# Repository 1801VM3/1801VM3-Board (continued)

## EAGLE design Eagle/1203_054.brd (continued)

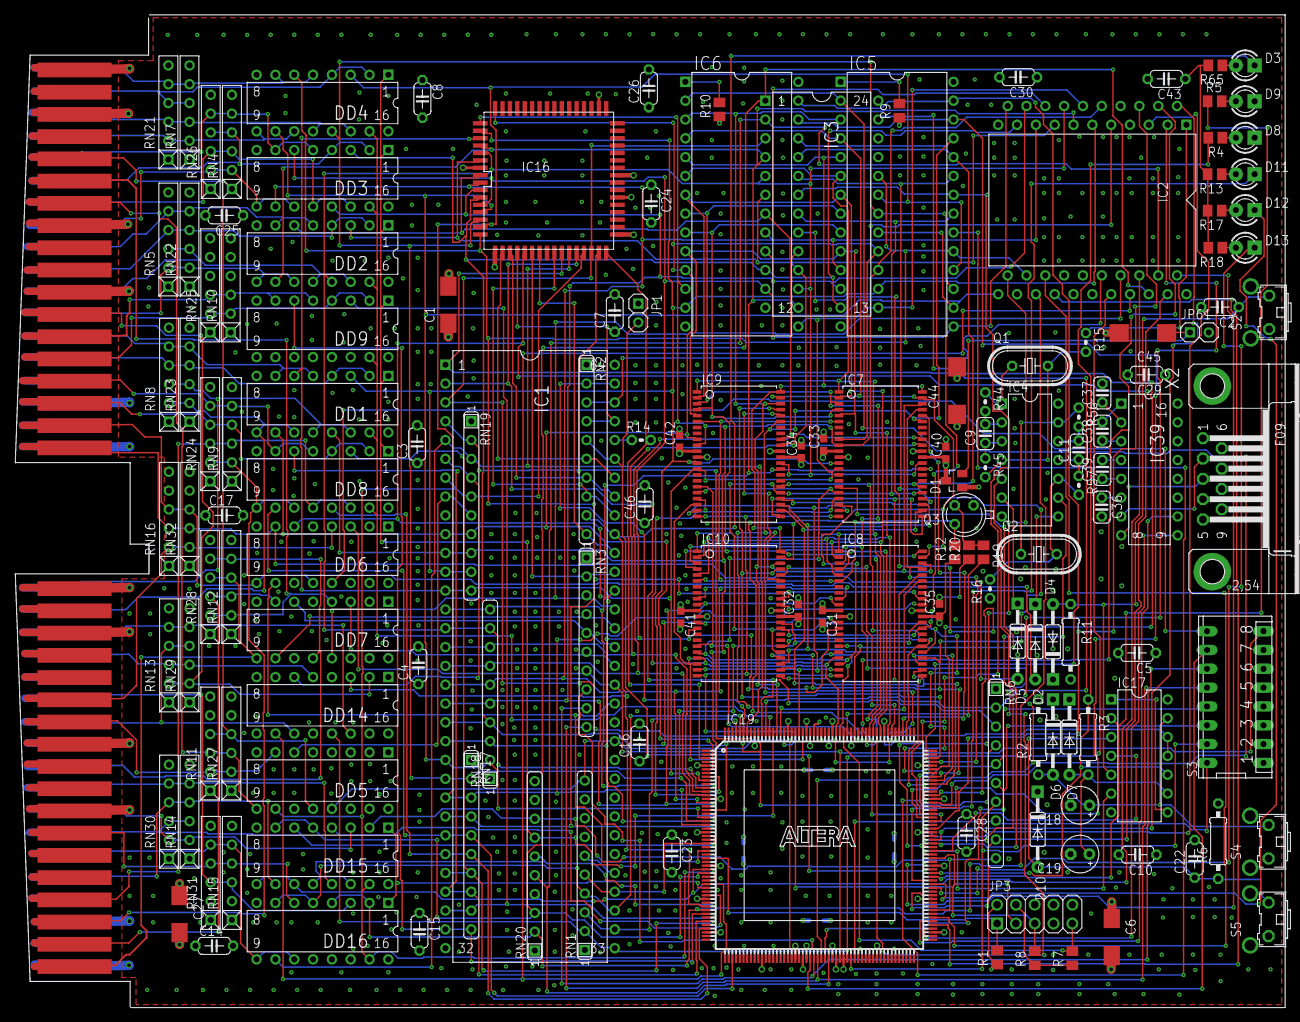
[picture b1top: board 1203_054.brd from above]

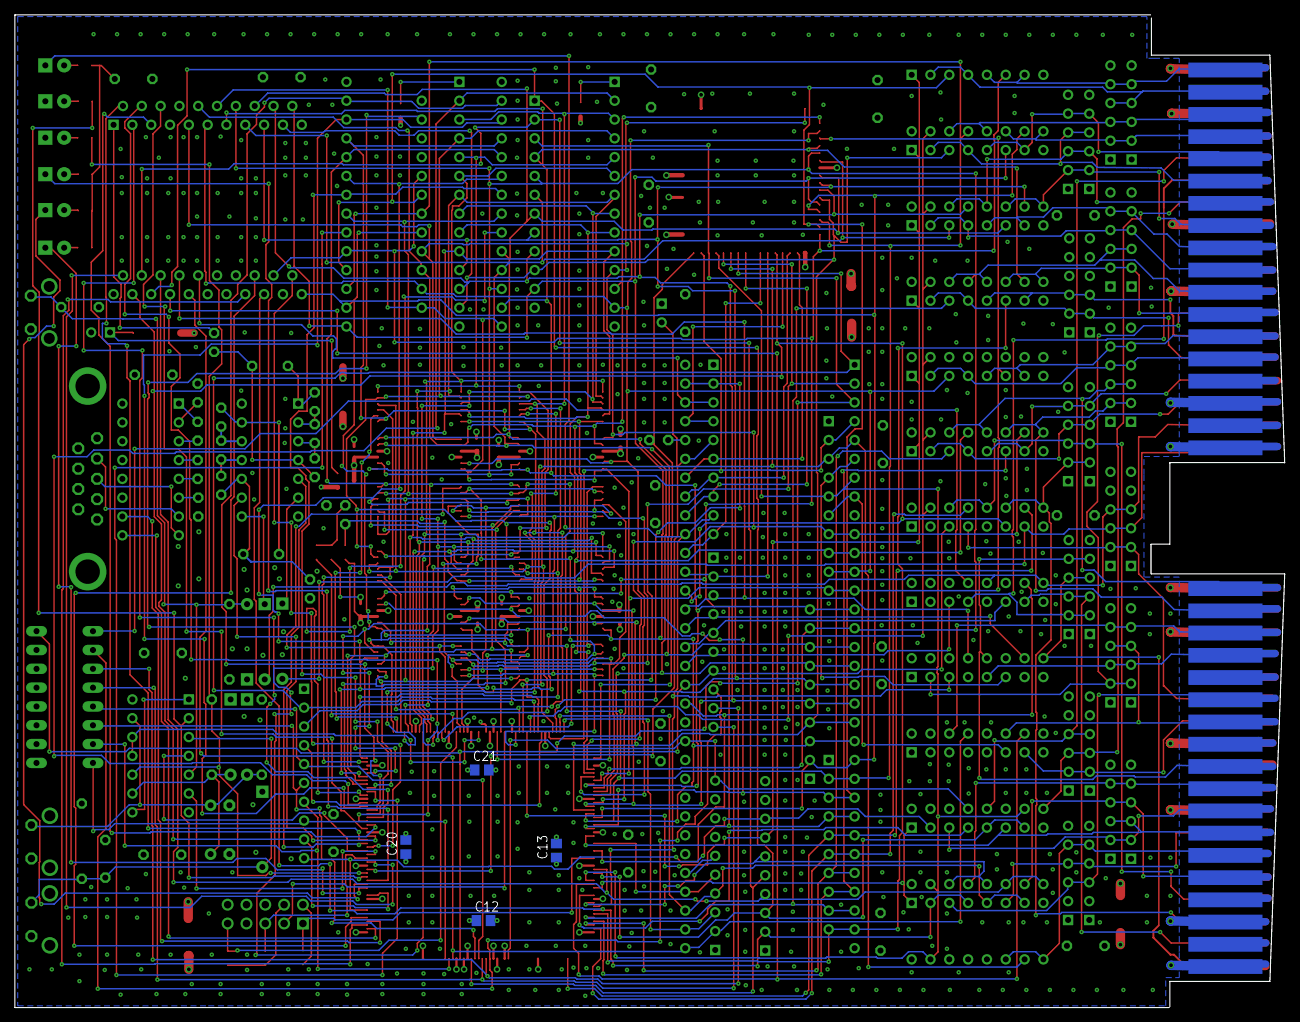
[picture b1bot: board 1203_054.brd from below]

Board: 3 copper layers, 171.4 x 134.0 mm, 154 parts (4 on the bottom side), 217 nets.

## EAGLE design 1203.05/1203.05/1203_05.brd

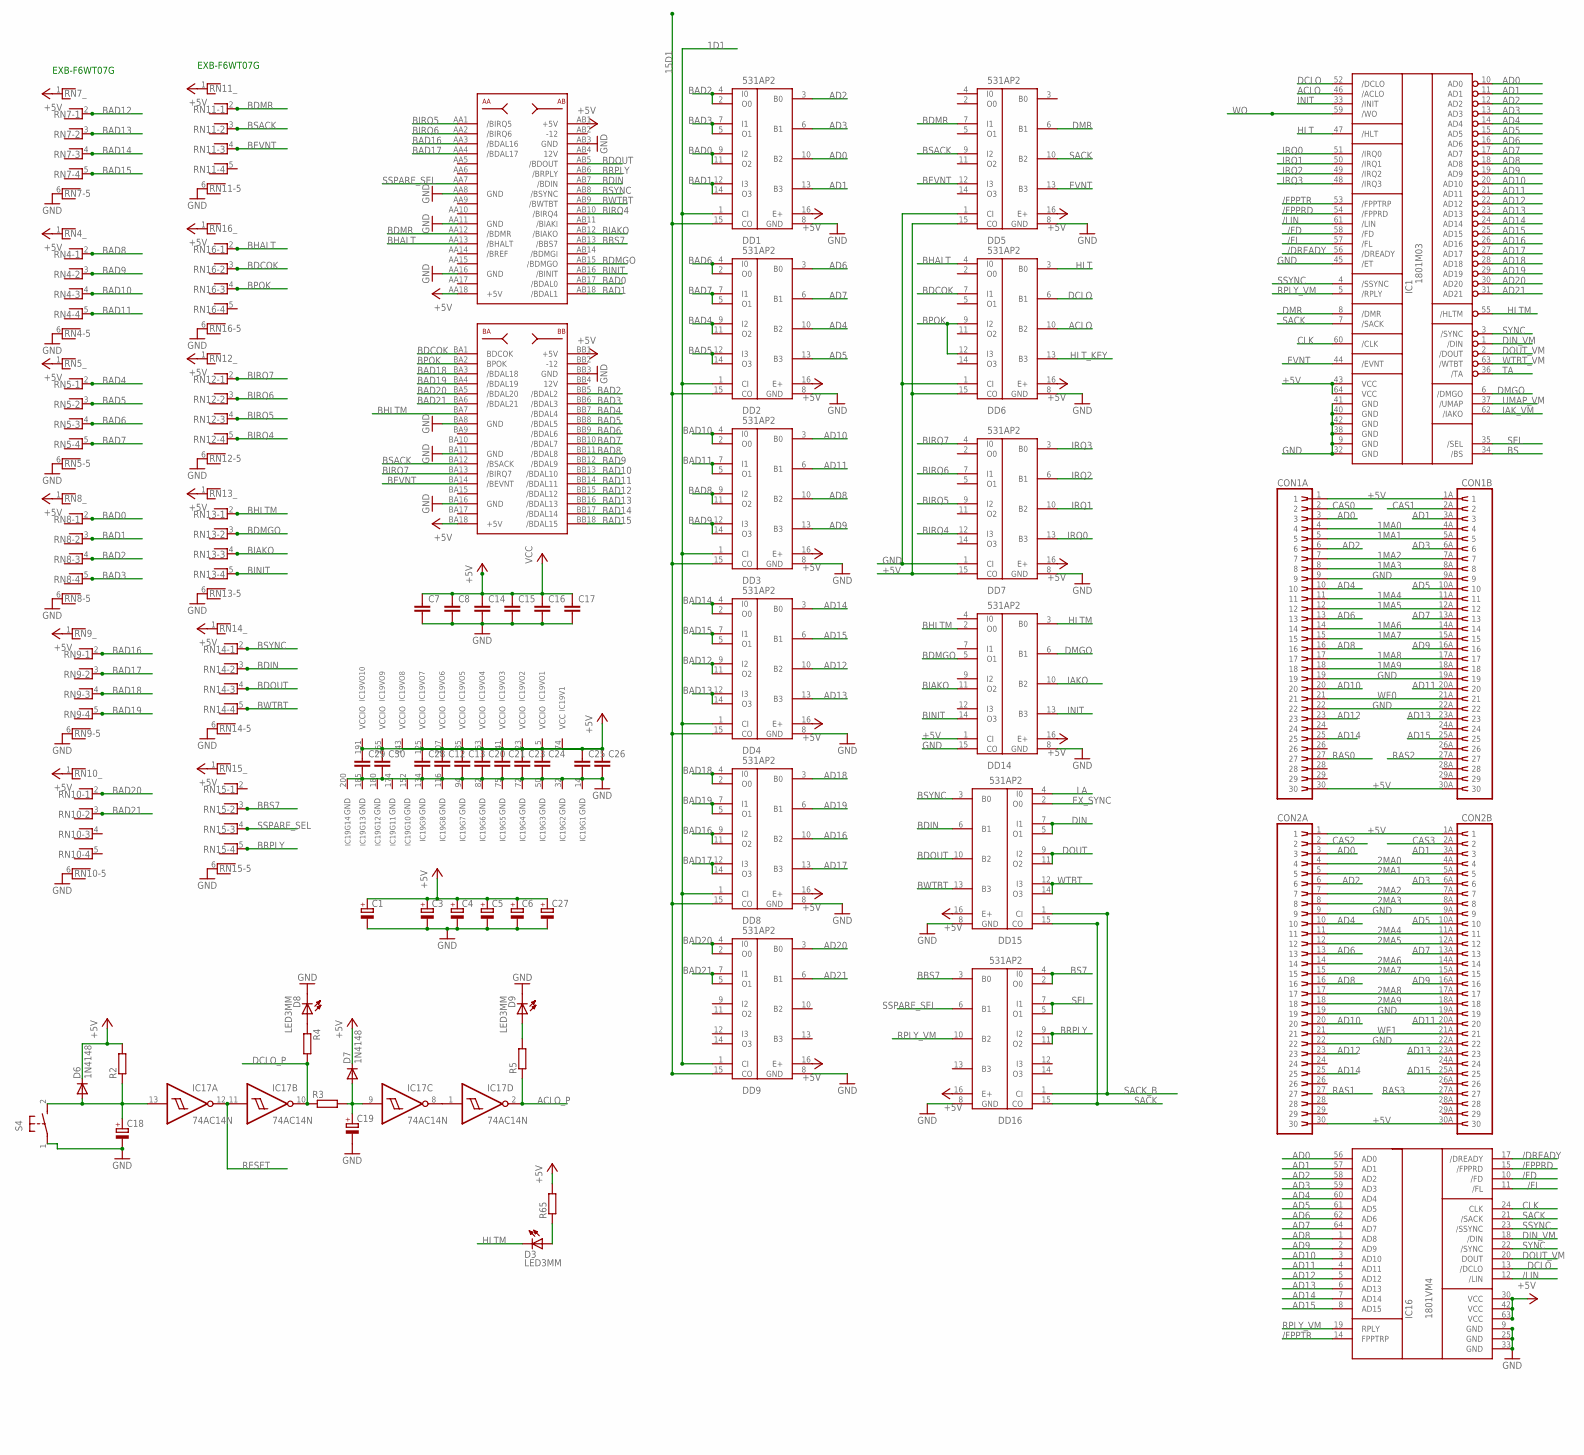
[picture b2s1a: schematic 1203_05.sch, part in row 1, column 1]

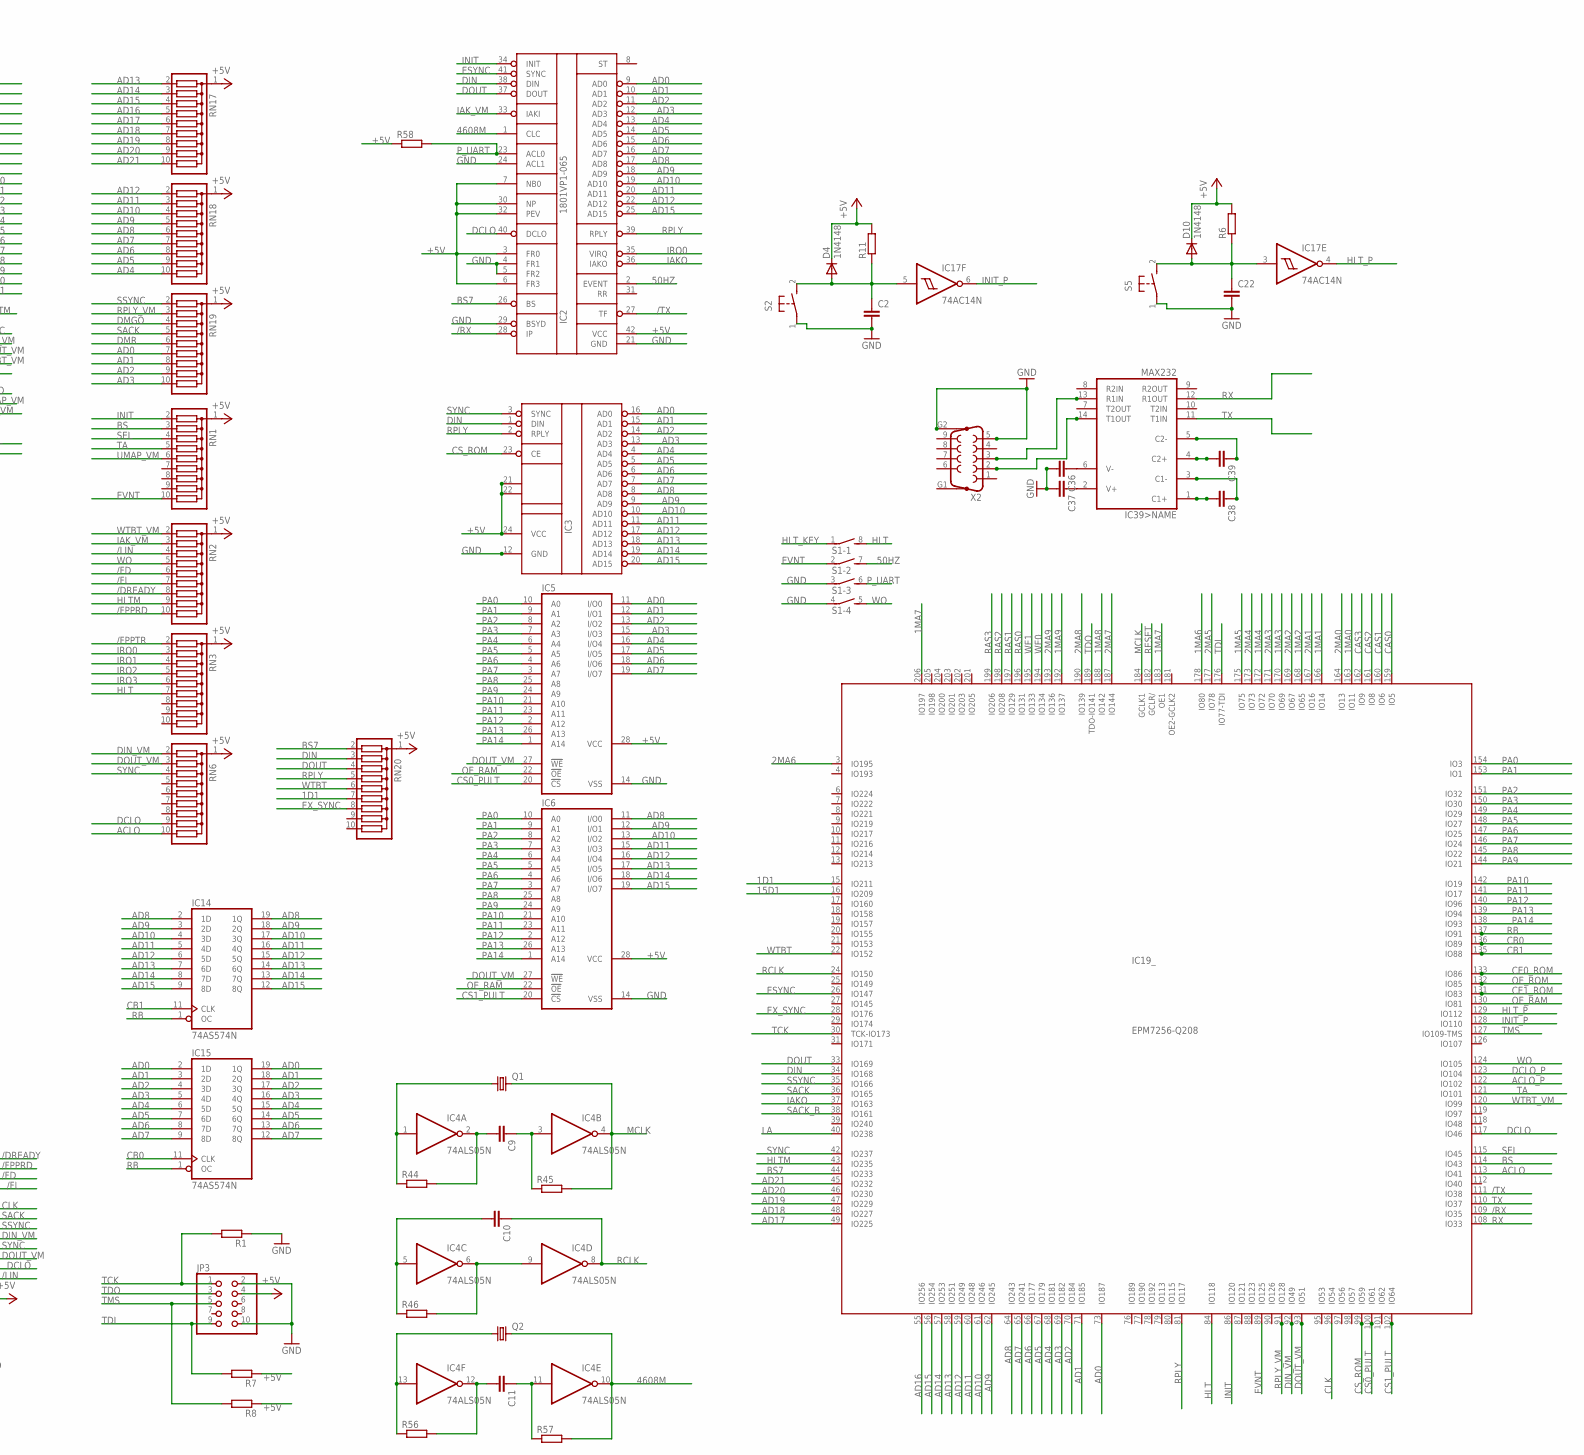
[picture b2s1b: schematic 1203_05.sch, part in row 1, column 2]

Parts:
C1, C3, C4, C6, C27: CPOL-EUCT6032; CT6032
C2, C7, C8, C14, C15, C16, C17, C22, C23, C24, C25, C26, C28, C29, C30: C-EU050-024X044; C050-024X044
C5: CPOL-EUB45181A; B45181A
C9, C11, C12, C13, C20, C21: C-EUC0805; C0805
C10, C36, C37, C38, C39: C-EU025-024X044; C025-024X044
C18, C19: CPOL-EUE2.5-5; E2,5-5
CON1, CON2: SIMM30-2
D3, D8, D9: LED3MM
D4, D6, D7, D10: 1N4148; DO35-10
DD1, DD2, DD3, DD4, DD5, DD6, DD7, DD8, DD9, DD14, DD15, DD16: 531AP2; DIL16
IC1: 1801M03; DIL64
IC2: 1801VP1-065; 1801
IC3: 1801RE2; DIL24
IC4: 74ALS05N; DIL14
IC5, IC6: 62832P; DIL28-3
IC14, IC15: 74AS574N; DIL20
IC16: 1801VM4
IC17: 74AC14N; DIL14
IC19: EPM7256-Q208; RQFP208
IC39: MAX232; DIL16
JP3: PINHD-2X5; 2X05
Q1, Q2: HC49U70
R1, R4, R5, R7, R8, R44, R45, R56, R57, R65: R-EU_M0805; M0805
R2, R3, R6, R11, R46, R58: R-EU_0207/10; 0207/10
RN1, RN2, RN3, RN6, RN17, RN18, RN19, RN20: G09R; SIL10
RN4, RN5, RN7, RN8, RN9, RN10, RN11, RN12, RN13, RN14, RN15, RN16: RNX5; RN-6
S1: DIP04SB
S2, S4, S5: 31-XX; B3F-31XX
X2: F09HP
XP1: CON1

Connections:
1D1: DD1.1 (CI), DD2.1 (CI), DD3.1 (CI), DD4.1 (CI), DD8.1 (CI), DD9.1 (CI), IC19.15 (IO211), RN20.7
1MA0: CON1.4, CON1.4A (4), IC19.163 (IO11)
1MA1: CON1.5, CON1.5A (5), IC19.166 (IO14)
1MA2: CON1.7, CON1.7A (7), IC19.168 (IO65)
1MA3: CON1.8, CON1.8A (8), IC19.170 (IO69)
1MA4: CON1.11, CON1.11A (11), IC19.172 (IO72)
1MA5: CON1.12, CON1.12A (12), IC19.175 (IO75)
1MA6: CON1.14, CON1.14A (14), IC19.178 (IO80)
1MA7: CON1.15, CON1.15A (15), IC19.183 (OE1), IC19.206 (IO197)
1MA8: CON1.17, CON1.17A (17), IC19.188 (IO142)
1MA9: CON1.18, CON1.18A (18), IC19.192 (IO137)
2MA0: CON2.4, CON2.4A (4), IC19.164 (IO13)
2MA1: CON2.5, CON2.5A (5), IC19.167 (IO16)
2MA2: CON2.7, CON2.7A (7), IC19.169 (IO67)
2MA3: CON2.8, CON2.8A (8), IC19.171 (IO70)
2MA4: CON2.11, CON2.11A (11), IC19.173 (IO73)
2MA5: CON2.12, CON2.12A (12), IC19.177 (IO78)
2MA6: CON2.14, CON2.14A (14), IC19.3 (IO195)
2MA7: CON2.15, CON2.15A (15), IC19.187 (IO144)
2MA8: CON2.17, CON2.17A (17), IC19.190 (IO139)
2MA9: CON2.18, CON2.18A (18), IC19.193 (IO136)
15D1: DD1.15 (CO), DD2.15 (CO), DD3.15 (CO), DD4.15 (CO), DD8.15 (CO), DD9.15 (CO), IC19.16 (IO209)
50HZ: IC2.2 (EVENT), S1.7 (2)
4608M: IC2.1 (CLC), IC4.10 (O), Q2.2, R57.2
+5V: C1.+, C3.+, C4.+, C5.+, C6.+, C7.1, C8.1, C12.1, C13.1, C14.1, C15.1, C16.1, C17.1, C20.1, C21.1, C23.1, C24.1, C25.1, C26.1, C27.+, C28.1, C29.1, C30.1, CON1.1, CON1.1A (1), CON1.30, CON1.30A (30), CON2.1, CON2.1A (1), CON2.30, CON2.30A (30), D4.K (C), D6.K (C), D7.K (C), D10.K (C), DD1.16 (E+), DD2.16 (E+), DD3.16 (E+), DD4.16 (E+), DD5.15 (CO), DD5.16 (E+), DD6.15 (CO), DD6.16 (E+), DD7.15 (CO), DD7.16 (E+), DD8.16 (E+), DD9.16 (E+), DD14.1 (CI), DD14.16 (E+), DD15.16 (E+), DD16.16 (E+), IC1.43 (VCC), IC1.64 (VCC), IC2.3 (FR0), IC2.6 (FR3), IC2.7 (NB0), IC2.30 (NP), IC2.32 (PEV), IC2.42 (VCC), IC3.21 (F0), IC3.22 (F1), IC3.24 (VCC), IC4.14 (VCC), IC5.28 (VCC), IC6.28 (VCC), IC14.20 (VCC), IC15.20 (VCC), IC16.30 (VCC), IC16.42 (VCC), IC16.63 (VCC), IC17.14 (VCC), IC19.5 (VCCIO), IC19.23 (VCCIO), IC19.41 (VCCIO), IC19.63 (VCCIO), IC19.74 (VCC), IC19.83 (VCC), IC19.85 (VCCIO), IC19.107 (VCCIO), IC19.125 (VCCIO), IC19.143 (VCCIO), IC19.165 (VCCIO), IC19.179 (VCC), IC19.186 (VCC), IC19.191 (VCCIO), JP3.4, R2.2, R6.2, R7.1, R8.1, R11.2, R58.1, R65.2, RN1.1, RN2.1, RN3.1, RN4.1, RN5.1, RN6.1, RN7.1, RN8.1, RN9.1, RN10.1, RN11.1, RN12.1, RN13.1, RN14.1, RN15.1, RN16.1, RN17.1, RN18.1, RN19.1, RN20.1, XP1.AA18 (+5V), XP1.AB1 (+5V), XP1.BA18 (+5V), XP1.BB1 (+5V)
/DREADY: IC1.56 (/DREADY), IC16.17 (/DREADY), RN2.8
/FD: IC1.58 (/FD), IC16.10 (/FD), RN2.6
/FL: IC1.57 (/FL), IC16.11 (/FL), RN2.7
/FPPRD: IC1.54 (/FPPRD), IC16.15 (/FPPRD), RN2.10
/FPPTR: IC1.53 (/FPPTRP), IC16.14 (FPPTRP), RN3.2
/LIN: IC1.61 (/LIN), IC16.12 (/LIN), RN2.4
/RX: IC2.28 (IP), IC19.109 (IO35)
/TX: IC2.27 (TF), IC19.111 (IO38)
ACLO: DD6.10 (B2), IC1.46 (/ACLO), IC19.113 (IO41), RN6.10
ACLO_P: IC17.2 (O), IC19.122 (IO102), R5.1
AD0: CON1.3, CON2.3, DD1.10 (B2), IC1.10 (AD0), IC2.9 (AD0), IC3.16 (AD0), IC5.11 (I/O0), IC15.2 (1D), IC15.19 (1Q), IC16.56 (AD0), IC19.73 (IO187), RN19.7
AD1: CON1.3A (3), CON2.3A (3), DD1.13 (B3), IC1.11 (AD1), IC2.10 (AD1), IC3.15 (AD1), IC5.12 (I/O1), IC15.3 (2D), IC15.18 (2Q), IC16.57 (AD1), IC19.71 (IO185), RN19.8
AD2: CON1.6, CON2.6, DD1.3 (B0), IC1.12 (AD2), IC2.11 (AD2), IC3.14 (AD2), IC5.13 (I/O2), IC15.4 (3D), IC15.17 (3Q), IC16.58 (AD2), IC19.70 (IO184), RN19.9
AD3: CON1.6A (6), CON2.6A (6), DD1.6 (B1), IC1.13 (AD3), IC2.12 (AD3), IC3.13 (AD3), IC5.15 (I/O3), IC15.5 (4D), IC15.16 (4Q), IC16.59 (AD3), IC19.69 (IO182), RN19.10
AD4: CON1.10, CON2.10, DD2.10 (B2), IC1.14 (AD4), IC2.13 (AD4), IC3.4 (AD4), IC5.16 (I/O4), IC15.6 (5D), IC15.15 (5Q), IC16.60 (AD4), IC19.68 (IO181), RN18.10
AD5: CON1.10A (10), CON2.10A (10), DD2.13 (B3), IC1.15 (AD5), IC2.14 (AD5), IC3.5 (AD5), IC5.17 (I/O5), IC15.7 (6D), IC15.14 (6Q), IC16.61 (AD5), IC19.67 (IO179), RN18.9
AD6: CON1.13, CON2.13, DD2.3 (B0), IC1.16 (AD6), IC2.15 (AD6), IC3.6 (AD6), IC5.18 (I/O6), IC15.8 (7D), IC15.13 (7Q), IC16.62 (AD6), IC19.66 (IO177), RN18.8
AD7: CON1.13A (13), CON2.13A (13), DD2.6 (B1), IC1.17 (AD7), IC2.16 (AD7), IC3.7 (AD7), IC5.19 (I/O7), IC15.9 (8D), IC15.12 (8Q), IC16.64 (AD7), IC19.65 (IO241), RN18.7
AD8: CON1.16, CON2.16, DD3.10 (B2), IC1.18 (AD8), IC2.17 (AD8), IC3.8 (AD8), IC6.11 (I/O0), IC14.2 (1D), IC14.19 (1Q), IC16.1 (AD8), IC19.64 (IO243), RN18.6
AD9: CON1.16A (16), CON2.16A (16), DD3.13 (B3), IC1.19 (AD9), IC2.18 (AD9), IC3.9 (AD9), IC6.12 (I/O1), IC14.3 (2D), IC14.18 (2Q), IC16.2 (AD9), IC19.62 (IO245), RN18.5
AD10: CON1.20, CON2.20, DD3.3 (B0), IC1.20 (AD10), IC2.19 (AD10), IC3.10 (AD10), IC6.13 (I/O2), IC14.4 (3D), IC14.17 (3Q), IC16.3 (AD10), IC19.61 (IO246), RN18.4
AD11: CON1.20A (20), CON2.20A (20), DD3.6 (B1), IC1.21 (AD11), IC2.20 (AD11), IC3.11 (AD11), IC6.15 (I/O3), IC14.5 (4D), IC14.16 (4Q), IC16.4 (AD11), IC19.60 (IO248), RN18.3
AD12: CON1.23, CON2.23, DD4.10 (B2), IC1.22 (AD12), IC2.22 (AD12), IC3.17 (AD12), IC6.16 (I/O4), IC14.6 (5D), IC14.15 (5Q), IC16.5 (AD12), IC19.59 (IO249), RN18.2
AD13: CON1.23A (23), CON2.23A (23), DD4.13 (B3), IC1.23 (AD13), IC3.18 (AD13), IC6.17 (I/O5), IC14.7 (6D), IC14.14 (6Q), IC16.6 (AD13), IC19.58 (IO251), RN17.2
AD14: CON1.25, CON2.25, DD4.3 (B0), IC1.24 (AD14), IC3.19 (AD14), IC6.18 (I/O6), IC14.8 (7D), IC14.13 (7Q), IC16.7 (AD14), IC19.57 (IO253), RN17.3
AD15: CON1.25A (25), CON2.25A (25), DD4.6 (B1), IC1.25 (AD15), IC2.25 (AD15), IC3.20 (AD15), IC6.19 (I/O7), IC14.9 (8D), IC14.12 (8Q), IC16.8 (AD15), IC19.56 (IO254), RN17.4
AD16: DD8.10 (B2), IC1.26 (AD16), IC19.55 (IO256), RN17.5
AD17: DD8.13 (B3), IC1.27 (AD17), IC19.49 (IO225), RN17.6
AD18: DD8.3 (B0), IC1.28 (AD18), IC19.48 (IO227), RN17.7
AD19: DD8.6 (B1), IC1.29 (AD19), IC19.47 (IO229), RN17.8
AD20: DD9.3 (B0), IC1.30 (AD20), IC19.46 (IO230), RN17.9
AD21: DD9.6 (B1), IC1.31 (AD21), IC19.45 (IO232), RN17.10
BAD0: DD1.9 (I2), DD1.11 (O2), RN8.2, XP1.AB17 (/BDAL0)
BAD1: DD1.12 (I3), DD1.14 (O3), RN8.3, XP1.AB18 (/BDAL1)
BAD2: DD1.2 (O0), DD1.4 (I0), RN8.4, XP1.BB5 (/BDAL2)
BAD3: DD1.5 (O1), DD1.7 (I1), RN8.5, XP1.BB6 (/BDAL3)
BAD4: DD2.9 (I2), DD2.11 (O2), RN5.2, XP1.BB7 (/BDAL4)
BAD5: DD2.12 (I3), DD2.14 (O3), RN5.3, XP1.BB8 (/BDAL5)
BAD6: DD2.2 (O0), DD2.4 (I0), RN5.4, XP1.BB9 (/BDAL6)
BAD7: DD2.5 (O1), DD2.7 (I1), RN5.5, XP1.BB10 (/BDAL7)
BAD8: DD3.9 (I2), DD3.11 (O2), RN4.2, XP1.BB11 (/BDAL8)
BAD9: DD3.12 (I3), DD3.14 (O3), RN4.3, XP1.BB12 (/BDAL9)
BAD10: DD3.2 (O0), DD3.4 (I0), RN4.4, XP1.BB13 (/BDAL10)
BAD11: DD3.5 (O1), DD3.7 (I1), RN4.5, XP1.BB14 (/BDAL11)
BAD12: DD4.9 (I2), DD4.11 (O2), RN7.2, XP1.BB15 (/BDAL12)
BAD13: DD4.12 (I3), DD4.14 (O3), RN7.3, XP1.BB16 (/BDAL13)
BAD14: DD4.2 (O0), DD4.4 (I0), RN7.4, XP1.BB17 (/BDAL14)
BAD15: DD4.5 (O1), DD4.7 (I1), RN7.5, XP1.BB18 (/BDAL15)
BAD16: DD8.9 (I2), DD8.11 (O2), RN9.2, XP1.AA3 (/BDAL16)
BAD17: DD8.12 (I3), DD8.14 (O3), RN9.3, XP1.AA4 (/BDAL17)
BAD18: DD8.2 (O0), DD8.4 (I0), RN9.4, XP1.BA3 (/BDAL18)
BAD19: DD8.5 (O1), DD8.7 (I1), RN9.5, XP1.BA4 (/BDAL19)
BAD20: DD9.2 (O0), DD9.4 (I0), RN10.2, XP1.BA5 (/BDAL20)
BAD21: DD9.5 (O1), DD9.7 (I1), RN10.3, XP1.BA6 (/BDAL21)
BBS7: DD16.3 (B0), RN15.3, XP1.AB13 (/BBS7)
BDCOK: DD6.7 (I1), RN16.3, XP1.BA1 (BDCOK)
BDIN: DD15.6 (B1), RN14.3, XP1.AB7 (/BDIN)
BDMGO: DD14.5 (O1), RN13.3, XP1.AB15 (/BDMGO)
BDMR: DD5.7 (I1), RN11.2, XP1.AA12 (/BDMR)
BDOUT: DD15.10 (B2), RN14.4, XP1.AB5 (/BDOUT)
BEVNT: DD5.12 (I3), RN11.4, XP1.BA14 (/BEVNT)
BHALT: DD6.4 (I0), RN16.2, XP1.AA13 (/BHALT)
BHLTM: DD14.2 (O0), RN13.2, XP1.BA7
BIAKO: DD14.11 (O2), RN13.4, XP1.AB12 (/BIAKO)
BINIT: DD14.14 (O3), RN13.5, XP1.AB16 (/BINIT)
BIRQ4: DD7.12 (I3), RN12.5, XP1.AB10 (/BIRQ4)
BIRQ5: DD7.9 (I2), RN12.4, XP1.AA1 (/BIRQ5)
BIRQ6: DD7.7 (I1), RN12.3, XP1.AA2 (/BIRQ6)
BIRQ7: DD7.4 (I0), RN12.2, XP1.BA13 (/BIRQ7)
BPOK: DD6.9 (I2), DD6.12 (I3), RN16.4, XP1.BA2 (BPOK)
BRPLY: DD16.9 (I2), DD16.11 (O2), RN15.5, XP1.AB6 (/BRPLY)
BS: IC1.34 (/BS), IC19.114 (IO43), RN1.3
BS7: DD16.2 (O0), DD16.4 (I0), IC2.26 (BS), IC19.44 (IO233), RN20.2
BSACK: DD5.9 (I2), RN11.3, XP1.BA12 (/BSACK)
BSYNC: DD15.3 (B0), RN14.2, XP1.AB8 (/BSYNC)
BWTBT: DD15.13 (B3), RN14.5, XP1.AB9 (/BWTBT)
CAS0: CON1.2, IC19.159 (IO5)
CAS1: CON1.2A (2), IC19.160 (IO6)
CAS2: CON2.2, IC19.161 (IO8)
CAS3: CON2.2A (2), IC19.162 (IO9)
CB0: IC15.11 (CLK), IC19.136 (IO89)
CB1: IC14.11 (CLK), IC19.135 (IO88)
CE0_ROM: IC19.133 (IO86)
CE1_ROM: IC19.131 (IO83)
CLK: IC1.60 (/CLK), IC16.24 (CLK), IC19.96 (IO54)
CS0_PULT: IC5.20 (!CS), IC19.100 (IO61)
CS1_PULT: IC6.20 (!CS), IC19.102 (IO64)
CS_ROM: IC3.23 (CE), IC19.99 (IO59)
DCLO: DD6.6 (B1), IC1.52 (/DCLO), IC2.40 (DCLO), IC16.13 (/DCLO), IC19.117 (IO46), RN6.9
DCLO_P: IC17.10 (O), IC19.123 (IO104), R3.1, R4.2
DIN: DD15.5 (O1), DD15.7 (I1), IC2.38 (DIN), IC3.1 (DIN), IC19.34 (IO168), RN20.3
DIN_VM: IC1.1 (/DIN), IC16.18 (/DIN), IC19.92 (IO49), RN6.2
DMGO: DD14.6 (B1), IC1.6 (/DMGO), RN19.4
DMR: DD5.6 (B1), IC1.8 (/DMR), RN19.6
DOUT: DD15.9 (I2), DD15.11 (O2), IC2.37 (DOUT), IC19.33 (IO169), RN20.4
DOUT_VM: IC1.2 (/DOUT), IC5.27 (!WE), IC6.27 (!WE), IC16.20 (DOUT), IC19.93 (IO51), RN6.3
ESYNC: IC2.41 (SYNC), IC19.26 (IO147)
EVNT: DD5.13 (B3), IC1.44 (/EVNT), IC19.89 (IO125), RN1.10, S1.2 (1)
EX_SYNC: DD15.2 (O0), IC19.28 (IO176), RN20.8
GND: C1.-, C2.2, C3.-, C4.-, C5.-, C6.-, C7.2, C8.2, C12.2, C13.2, C14.2, C15.2, C16.2, C17.2, C18.-, C19.-, C20.2, C21.2, C22.2, C23.2, C24.2, C25.2, C26.2, C27.-, C28.2, C29.2, C30.2, C36.2, C37.2, CON1.9, CON1.9A (9), CON1.19, CON1.19A (19), CON1.22, CON1.22A (22), CON2.9, CON2.9A (9), CON2.19, CON2.19A (19), CON2.22, CON2.22A (22), D8.K (C), D9.K (C), DD1.8 (GND), DD2.8 (GND), DD3.8 (GND), DD4.8 (GND), DD5.1 (CI), DD5.8 (GND), DD6.1 (CI), DD6.8 (GND), DD7.1 (CI), DD7.8 (GND), DD8.8 (GND), DD9.8 (GND), DD14.8 (GND), DD14.15 (CO), DD15.8 (GND), DD16.8 (GND), IC1.9 (GND), IC1.32 (GND), IC1.38 (GND), IC1.40 (GND), IC1.41 (GND), IC1.42 (GND), IC1.45 (/ET), IC2.4 (FR1), IC2.5 (FR2), IC2.21 (GND), IC2.24 (ACL1), IC2.29 (BSYD), IC3.12 (GND), IC4.7 (GND), IC5.14 (VSS), IC6.14 (VSS), IC14.10 (GND), IC15.10 (GND), IC16.9 (GND), IC16.25 (GND), IC16.33 (GND), IC17.7 (GND), IC19.14 (GND), IC19.32 (GND), IC19.50 (GND), IC19.72 (GND), IC19.75 (GND), IC19.82 (GND), IC19.94 (GND), IC19.116 (GND), IC19.134 (GND), IC19.152 (GND), IC19.174 (GND), IC19.180 (GND), IC19.185 (GND), IC19.200 (GND), JP3.2, JP3.10, R1.1, RN4.6, RN5.6, RN7.6, RN8.6, RN9.6, RN10.6, RN11.6, RN12.6, RN13.6, RN14.6, RN15.6, RN16.6, S1.3 (1), S1.4 (1), S2.1, S4.1, S5.1, X2.5, X2.G2, XP1.AA8 (GND), XP1.AA11 (GND), XP1.AA16 (GND), XP1.AB3 (GND), XP1.BA8 (GND), XP1.BA11 (GND), XP1.BA16 (GND), XP1.BB3 (GND)
HLT: DD6.3 (B0), IC1.47 (/HLT), IC19.84 (IO118), RN3.7, S1.8 (2)
HLTM: D3.K (C), DD14.3 (B0), IC1.55 (/HLTM), IC19.43 (IO235), RN2.9
HLT_KEY: DD6.13 (B3), S1.1
HLT_P: IC17.4 (O), IC19.129 (IO112)
IAKO: DD14.10 (B2), IC2.36 (IAKO), IC19.37 (IO163)
IAK_VM: IC1.62 (/IAKO), IC2.33 (IAKI), RN2.3
INIT: DD14.13 (B3), IC1.33 (/INIT), IC2.34 (INIT), IC19.86 (IO120), RN1.2
INIT_P: IC17.6 (O), IC19.128 (IO110)
IRQ0: DD7.13 (B3), IC1.51 (/IRQ0), IC2.35 (VIRQ), RN3.3
IRQ1: DD7.10 (B2), IC1.50 (/IRQ1), RN3.4
IRQ2: DD7.6 (B1), IC1.49 (/IRQ2), RN3.5
IRQ3: DD7.3 (B0), IC1.48 (/IRQ3), RN3.6
LA: DD15.4 (I0), IC19.40 (IO238)
MCLK: IC4.4 (O), IC19.184 (GCLK1), Q1.2, R45.2
unnamed: IC17.1 (I), IC17.8 (O)
unnamed: C38.1, IC39.3 (C1-)
unnamed: D9.A, R5.2
unnamed: C18.+, D6.A, IC17.13 (I), R2.1, S4.2
unnamed: IC4.1 (I), Q1.1, R44.1
unnamed: D3.A, R65.1
unnamed: C9.2, IC4.2 (O), R44.2
unnamed: C19.+, D7.A, IC17.9 (I), R3.2
unnamed: D8.A, R4.1
unnamed: C22.1, D10.A, IC17.3 (I), R6.1, S5.2
unnamed: C2.1, D4.A, IC17.5 (I), R11.1, S2.2
unnamed: IC4.13 (I), Q2.1, R56.1
unnamed: C9.1, IC4.3 (I), R45.1
unnamed: IC4.6 (O), IC4.9 (I), R46.2
unnamed: C10.2, IC4.5 (I), R46.1
unnamed: C38.2, IC39.1 (C1+)
unnamed: C39.2, IC39.4 (C2+)
unnamed: C39.1, IC39.5 (C2-)
unnamed: IC39.14 (T1OUT), X2.2
unnamed: IC39.13 (R1IN), X2.3
unnamed: C36.1, IC39.6 (V-)
unnamed: C37.1, IC39.2 (V+)
unnamed: C11.2, IC4.12 (O), R56.2
unnamed: C11.1, IC4.11 (I), R57.1
OE_RAM: IC5.22 (!OE), IC6.22 (!OE), IC19.130 (IO81)
OE_ROM: IC19.132 (IO85)
PA0: IC5.10 (A0), IC6.10 (A0), IC19.154 (IO3)
PA1: IC5.9 (A1), IC6.9 (A1), IC19.153 (IO1)
PA2: IC5.8 (A2), IC6.8 (A2), IC19.151 (IO32)
PA3: IC5.7 (A3), IC6.7 (A3), IC19.150 (IO30)
PA4: IC5.6 (A4), IC6.6 (A4), IC19.149 (IO29)
PA5: IC5.5 (A5), IC6.5 (A5), IC19.148 (IO27)
PA6: IC5.4 (A6), IC6.4 (A6), IC19.147 (IO25)
PA7: IC5.3 (A7), IC6.3 (A7), IC19.146 (IO24)
PA8: IC5.25 (A8), IC6.25 (A8), IC19.145 (IO22)
PA9: IC5.24 (A9), IC6.24 (A9), IC19.144 (IO21)
PA10: IC5.21 (A10), IC6.21 (A10), IC19.142 (IO19)
PA11: IC5.23 (A11), IC6.23 (A11), IC19.141 (IO17)
PA12: IC5.2 (A12), IC6.2 (A12), IC19.140 (IO96)
PA13: IC5.26 (A13), IC6.26 (A13), IC19.139 (IO94)
PA14: IC5.1 (A14), IC6.1 (A14), IC19.138 (IO93)
P_UART: IC2.23 (ACL0), R58.2, S1.6 (2)
RAS0: CON1.27, IC19.196 (IO131)
RAS1: CON2.27, IC19.197 (IO129)
RAS2: CON1.27A (27), IC19.198 (IO208)
RAS3: CON2.27A (27), IC19.199 (IO206)
RB: IC14.1 (OC), IC15.1 (OC), IC19.137 (IO91)
RCLK: C10.1, IC4.8 (O), IC19.24 (IO150)
RESET: IC17.11 (I), IC17.12 (O), IC19.182 (GCLR/)
RPLY: IC2.39 (RPLY), IC3.2 (RPLY), IC19.81 (IO117), RN20.5
RPLY_VM: DD16.10 (B2), IC1.5 (/RPLY), IC16.19 (RPLY), IC19.91 (IO128), RN19.3
RX: IC19.108 (IO33), IC39.12 (R1OUT)
SACK: DD5.10 (B2), DD15.15 (CO), DD16.15 (CO), IC1.7 (/SACK), IC16.21 (/SACK), IC19.36 (IO165), RN19.5
SACK_B: DD15.1 (CI), DD16.1 (CI), IC19.38 (IO161)
SEL: DD16.5 (O1), DD16.7 (I1), IC1.35 (/SEL), IC19.115 (IO45), RN1.4
SSPARE_SEL: DD16.6 (B1), RN15.4, XP1.AA7
SSYNC: IC1.4 (/SSYNC), IC16.23 (/SSYNC), IC19.35 (IO166), RN19.2
SYNC: IC1.3 (/SYNC), IC3.3 (SYNC), IC16.22 (/SYNC), IC19.42 (IO237), RN6.4
TA: IC1.36 (/TA), IC19.121 (IO101), RN1.5
TCK: IC19.30 (TCK-IO173), JP3.1, R1.2
TDI: IC19.176 (IO77-TDI), JP3.9, R7.2
TDO: IC19.189 (TDO-IO141), JP3.3
TMS: IC19.127 (IO109-TMS), JP3.5, R8.2
TX: IC19.110 (IO37), IC39.11 (T1IN)
UMAP_VM: IC1.37 (/UMAP), RN1.6
WE0: CON1.21, CON1.21A (21), IC19.194 (IO134)
WE1: CON2.21, CON2.21A (21), IC19.195 (IO133)
WO: IC1.59 (/WO), IC19.124 (IO105), RN2.5, S1.5 (2)
WTBT: DD15.12 (I3), DD15.14 (O3), IC19.22 (IO152), RN20.6
WTBT_VM: IC1.63 (/WTBT), IC19.120 (IO99), RN2.2

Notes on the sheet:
EXB-F6WT07G

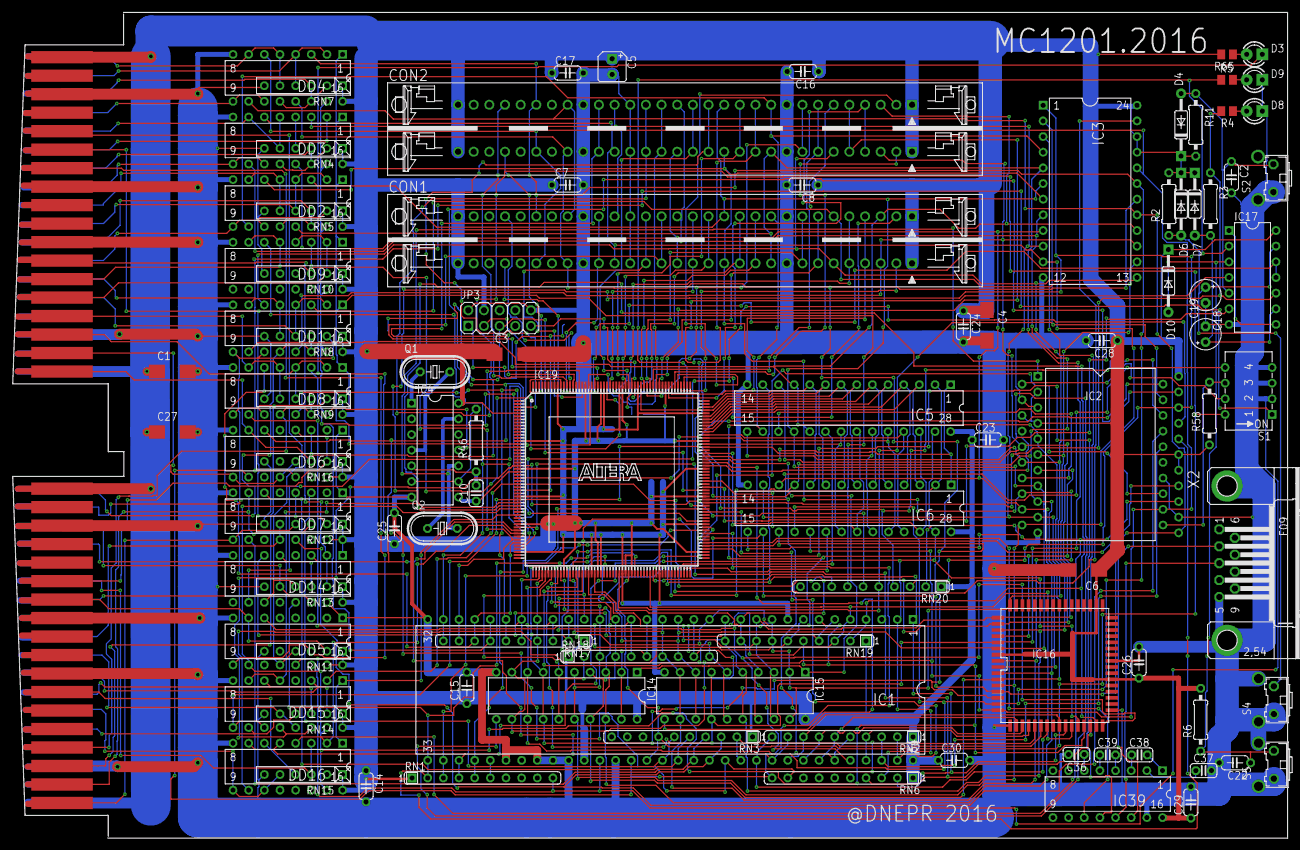
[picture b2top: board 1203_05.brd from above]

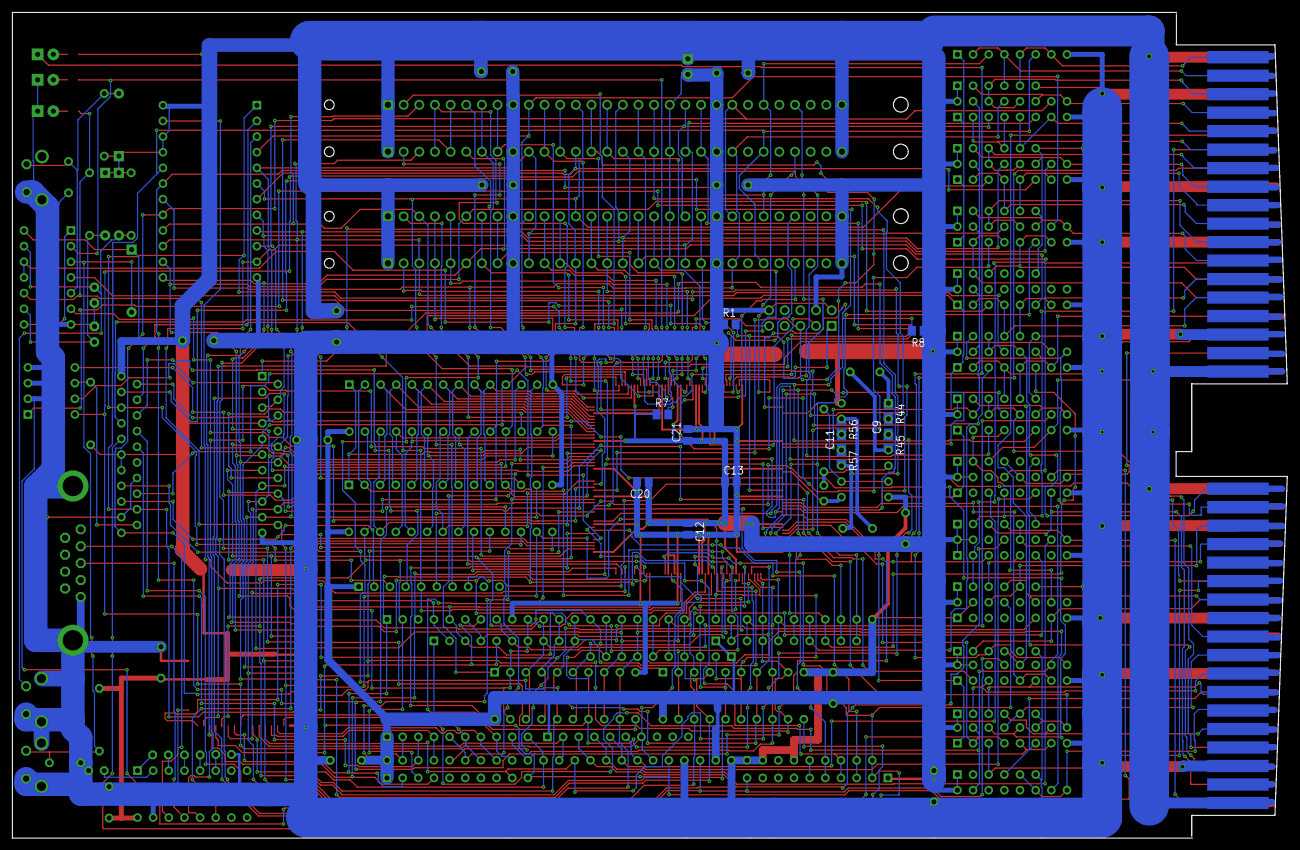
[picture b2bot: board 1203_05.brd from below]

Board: 3 copper layers, 206.9 x 134.0 mm, 112 parts (13 on the bottom side), 206 nets.

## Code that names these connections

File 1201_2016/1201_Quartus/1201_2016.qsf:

# -------------------------------------------------------------------------- #
#
# Copyright (C) 1991-2013 Altera Corporation
# Your use of Altera Corporation's design tools, logic functions 
# and other software and tools, and its AMPP partner logic 
# functions, and any output files from any of the foregoing 
# (including device programming or simulation files), and any 
# associated documentation or information are expressly subject 
# to the terms and conditions of the Altera Program License 
# Subscription Agreement, Altera MegaCore Function License 
# Agreement, or other applicable license agreement, including, 
# without limitation, that your use is for the sole purpose of 
# programming logic devices manufactured by Altera and sold by 
# Altera or its authorized distributors.  Please refer to the 
# applicable agreement for further details.
#
# -------------------------------------------------------------------------- #
#
# Quartus II 64-Bit
# Version 13.0.1 Build 232 06/12/2013 Service Pack 1 SJ Web Edition
# Date created = 15:27:10  November 07, 2016
#
# -------------------------------------------------------------------------- #
#
# Notes:
#
# 1) The default values for assignments are stored in the file:
#		1201_2016_assignment_defaults.qdf
#    If this file doesn't exist, see file:
#		assignment_defaults.qdf
#
# 2) Altera recommends that you do not modify this file. This
#    file is updated automatically by the Quartus II software
#    and any changes you make may be lost or overwritten.
#
# -------------------------------------------------------------------------- #


set_global_assignment -name FAMILY MAX7000S
set_global_assignment -name DEVICE "EPM7256SRI208-10"
set_global_assignment -name TOP_LEVEL_ENTITY 1201_2016
set_global_assignment -name ORIGINAL_QUARTUS_VERSION "13.0 SP1"
set_global_assignment -name PROJECT_CREATION_TIME_DATE "15:27:10  NOVEMBER 07, 2016"
set_global_assignment -name LAST_QUARTUS_VERSION "13.0 SP1"
set_global_assignment -name PROJECT_OUTPUT_DIRECTORY output_files
set_global_assignment -name DEVICE_FILTER_PIN_COUNT 208
set_global_assignment -name DEVICE_FILTER_SPEED_GRADE 10
set_global_assignment -name ERROR_CHECK_FREQUENCY_DIVISOR "-1"
set_global_assignment -name EDA_SIMULATION_TOOL "ModelSim (Verilog)"
set_global_assignment -name EDA_TIME_SCALE "1 ps" -section_id eda_simulation
set_global_assignment -name EDA_OUTPUT_DATA_FORMAT "VERILOG HDL" -section_id eda_simulation
set_global_assignment -name MAX7000_DEVICE_IO_STANDARD TTL
set_location_assignment PIN_6 -to BAD[0]
set_location_assignment PIN_7 -to BAD[1]
set_location_assignment PIN_8 -to BAD[2]
set_location_assignment PIN_9 -to BAD[3]
set_location_assignment PIN_10 -to BAD[4]
set_location_assignment PIN_11 -to BAD[5]
set_location_assignment PIN_12 -to BAD[6]
set_location_assignment PIN_13 -to BAD[7]
set_location_assignment PIN_15 -to BAD[8]
set_location_assignment PIN_16 -to BAD[9]
set_location_assignment PIN_17 -to BAD[10]
set_location_assignment PIN_18 -to BAD[11]
set_location_assignment PIN_19 -to BAD[12]
set_location_assignment PIN_20 -to BAD[13]
set_location_assignment PIN_21 -to BAD[14]
set_location_assignment PIN_22 -to BAD[15]
set_location_assignment PIN_55 -to ADR[16]
set_location_assignment PIN_45 -to ADR[21]
set_location_assignment PIN_46 -to ADR[20]
set_location_assignment PIN_47 -to ADR[19]
set_location_assignment PIN_48 -to ADR[18]
set_location_assignment PIN_49 -to ADR[17]
set_location_assignment PIN_204 -to SEL
set_location_assignment PIN_205 -to BS
set_location_assignment PIN_44 -to BS7
set_location_assignment PIN_111 -to TXin
set_location_assignment PIN_110 -to TXout
set_location_assignment PIN_108 -to RXin
set_location_assignment PIN_109 -to RXout
set_location_assignment PIN_195 -to 1D1
set_location_assignment PIN_196 -to 15D1
set_location_assignment PIN_3 -to VM3_CLK
set_location_assignment PIN_177 -to SA[19]
set_location_assignment PIN_178 -to SA[18]
set_location_assignment PIN_187 -to SA[17]
set_location_assignment PIN_188 -to SA[16]
set_location_assignment PIN_192 -to SA[15]
set_location_assignment PIN_146 -to SA[14]
set_location_assignment PIN_147 -to SA[13]
set_location_assignment PIN_148 -to SA[12]
set_location_assignment PIN_149 -to SA[11]
set_location_assignment PIN_150 -to SA[10]
set_location_assignment PIN_159 -to SA[9]
set_location_assignment PIN_193 -to SA[8]
set_location_assignment PIN_194 -to SA[7]
set_location_assignment PIN_171 -to SA[6]
set_location_assignment PIN_170 -to SA[5]
set_location_assignment PIN_169 -to SA[4]
set_location_assignment PIN_168 -to SA[3]
set_location_assignment PIN_167 -to SA[2]
set_location_assignment PIN_166 -to SA[1]
set_location_assignment PIN_164 -to SA[0]
set_location_assignment PIN_160 -to SCE0
set_location_assignment PIN_161 -to SCE1
set_location_assignment PIN_162 -to SCE2
set_location_assignment PIN_163 -to SCE3
set_location_assignment PIN_172 -to WE0
set_location_assignment PIN_173 -to WE1
set_location_assignment PIN_151 -to CSROM
set_location_assignment PIN_153 -to S_OE0
set_location_assignment PIN_154 -to S_OE1
set_location_assignment PIN_175 -to SRAM_CE_G
set_location_assignment PIN_24 -to BDIN
set_location_assignment PIN_34 -to DIN_
set_location_assignment PIN_33 -to DOUT_
set_location_assignment PIN_197 -to DIN_VM
set_location_assignment PIN_198 -to DOUT_VM
set_location_assignment PIN_28 -to EX_SYNC
set_location_assignment PIN_126 -to ESYNC
set_location_assignment PIN_40 -to LA
set_location_assignment PIN_184 -to Main_CLK
set_location_assignment PIN_202 -to RPLY_VM
set_location_assignment PIN_81 -to RPLY
set_location_assignment PIN_201 -to SSYNC
set_location_assignment PIN_199 -to SYNC_VM
set_location_assignment PIN_203 -to WTBT_VM
set_location_assignment PIN_42 -to WTBT_
set_location_assignment PIN_36 -to SACK
set_location_assignment PIN_38 -to SACK_B
set_location_assignment PIN_122 -to ACLO_P
set_location_assignment PIN_123 -to DCLO_P
set_location_assignment PIN_128 -to INIT_P
set_location_assignment PIN_129 -to HLTM_P
set_location_assignment PIN_113 -to ACLO
set_location_assignment PIN_117 -to DCLO
set_location_assignment PIN_86 -to INIT
set_location_assignment PIN_84 -to HLT
set_location_assignment PIN_132 -to 100HZ
set_location_assignment PIN_71 -to EVNT
set_location_assignment PIN_135 -to FR[3]
set_location_assignment PIN_136 -to FR[2]
set_location_assignment PIN_137 -to FR[1]
set_location_assignment PIN_138 -to FR[0]
set_location_assignment PIN_130 -to PULT
set_global_assignment -name USE_CONFIGURATION_DEVICE ON
set_global_assignment -name RESERVE_ALL_UNUSED_PINS_NO_OUTPUT_GND "AS INPUT TRI-STATED"
set_location_assignment PIN_87 -to HK6
set_location_assignment PIN_88 -to HK7
set_location_assignment PIN_80 -to HK5
set_location_assignment PIN_121 -to EVNT_LED
set_location_assignment PIN_124 -to WO
set_global_assignment -name OPTIMIZE_HOLD_TIMING OFF
set_global_assignment -name OPTIMIZE_MULTI_CORNER_TIMING OFF
set_global_assignment -name FITTER_EFFORT "STANDARD FIT"
set_location_assignment PIN_120 -to LED2
set_location_assignment PIN_133 -to ACLO_F
set_global_assignment -name BDF_FILE 1201_2016.bdf
set_global_assignment -name VERILOG_FILE 065_c.v
set_location_assignment PIN_131 -to DCLO_F
set_location_assignment PIN_76 -to HK1
set_location_assignment PIN_142 -to ROM1
set_location_assignment PIN_140 -to ROM3
set_location_assignment PIN_144 -to ROMCE0
set_location_assignment PIN_145 -to ROMCE1
set_location_assignment PIN_139 -to ROMOE
set_location_assignment PIN_141 -to ROM2
set_location_assignment PIN_79 -to HK4
set_location_assignment PIN_77 -to HK2

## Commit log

2017-02-22 try 2
2017-02-23 Eagle files added
